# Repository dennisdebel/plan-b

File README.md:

Wemos Midi Roll Project
=====================================

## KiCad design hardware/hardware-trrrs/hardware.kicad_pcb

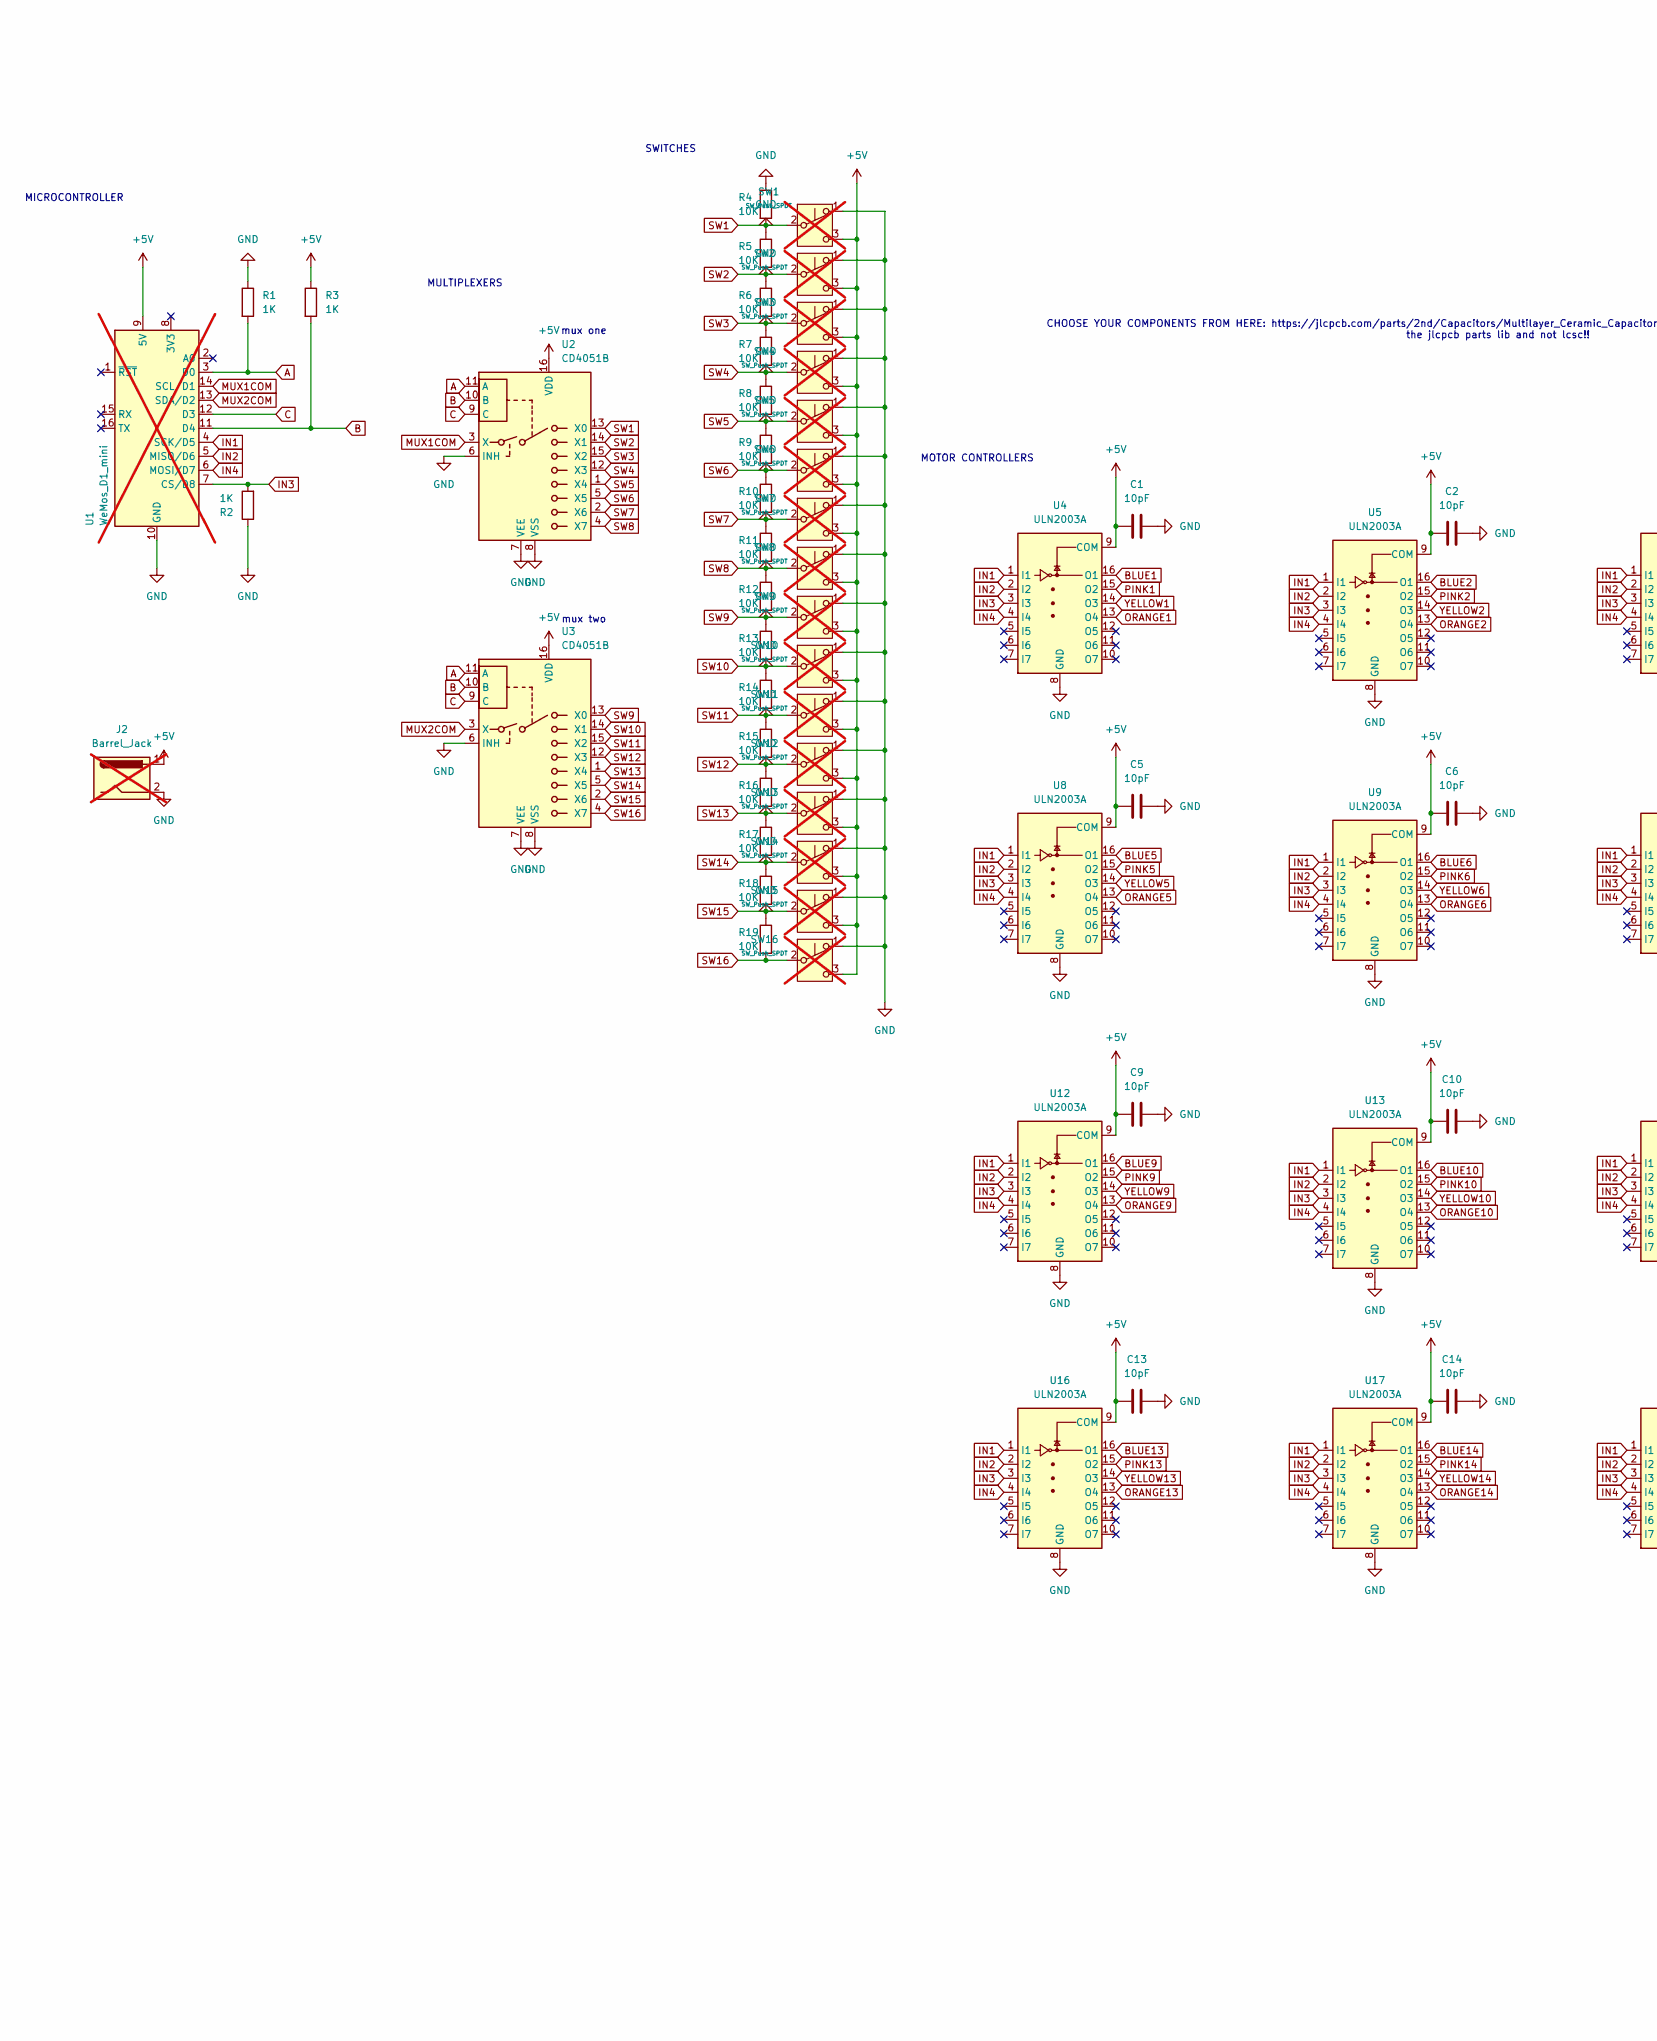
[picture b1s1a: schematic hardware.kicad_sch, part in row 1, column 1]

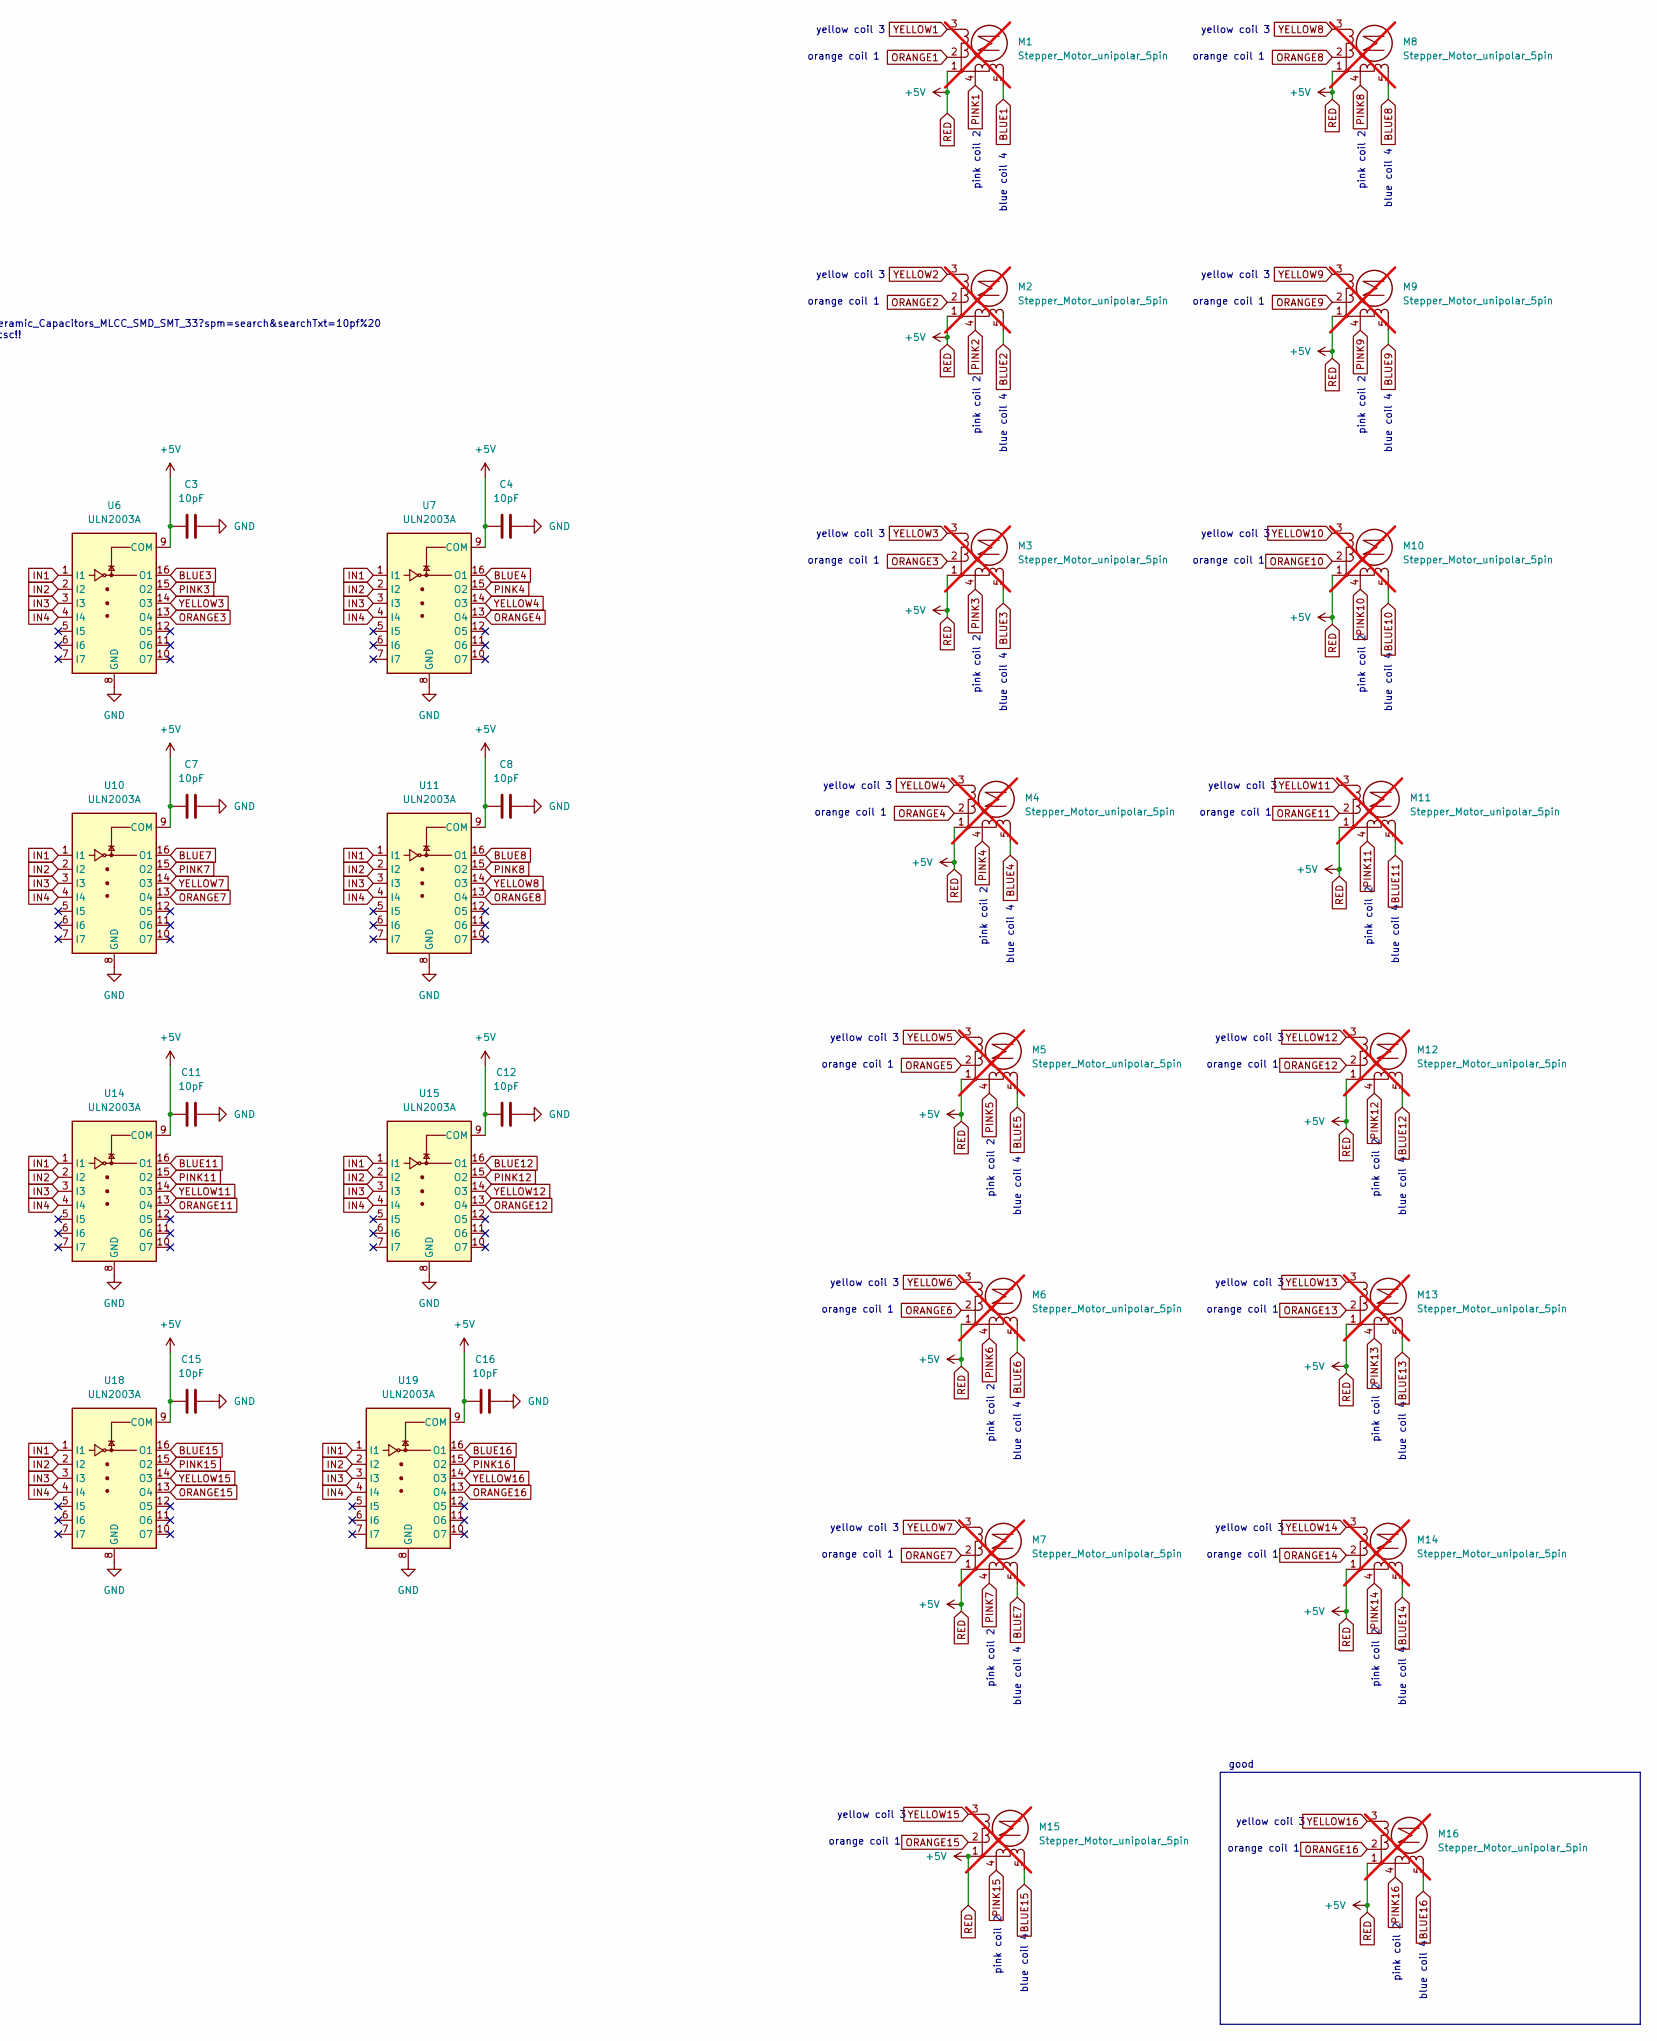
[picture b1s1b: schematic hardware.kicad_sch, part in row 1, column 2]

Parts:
C1, C2, C3, C4, C5, C6, C7, C8, C9, C10, C11, C12, C13, C14, C15, C16: 10pF; C_0402_1005Metric; LCSC PN C1545
J2: Barrel_Jack; BarrelJack_CUI_PJ-063AH_Horizontal; LCSC PN C22434582; not fitted
M1, M2, M3, M4, M5, M6, M7, M8, M9, M10, M11, M12, M13, M14, M15, M16: Stepper_Motor_unipolar_5pin; AUDIO-SMD_STX-3542-5N-G-TR; not fitted
R1, R2, R3: 1K; R_0805_2012Metric; LCSC PN C25623
R4, R5, R6, R7, R8, R9, R10, R11, R12, R13, R14, R15, R16, R17, R18, R19: 10K; R_0805_2012Metric; LCSC PN C2930231
SW1, SW2, SW3, SW4, SW5, SW6, SW7, SW8, SW9, SW10, SW11, SW12, SW13, SW14, SW15, SW16: SW_Push_SPDT; SW_MS0850502F030P1A-fixed; not fitted
U1: WeMos_D1_mini; WEMOS_D1_mini_light; not fitted
U2, U3: CD4051B; SOIC-16_3.9x9.9mm_P1.27mm; LCSC PN C21379
U4, U5, U6, U7, U8, U9, U10, U11, U12, U13, U14, U15, U16, U17, U18, U19: ULN2003A; SOIC-16_3.9x9.9mm_P1.27mm; LCSC PN C7512

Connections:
A: R1.2, U1.3 (D0), U2.11 (A), U3.11 (A)
B: R3.2, U1.11 (D4), U2.10 (B), U3.10 (B)
BLUE1: M1.5, U4.16 (O1)
BLUE2: M2.5, U5.16 (O1)
BLUE3: M3.5, U6.16 (O1)
BLUE4: M4.5, U7.16 (O1)
BLUE5: M5.5, U8.16 (O1)
BLUE6: M6.5, U9.16 (O1)
BLUE7: M7.5, U10.16 (O1)
BLUE8: M8.5, U11.16 (O1)
BLUE9: M9.5, U12.16 (O1)
BLUE10: M10.5, U13.16 (O1)
BLUE11: M11.5, U14.16 (O1)
BLUE12: M12.5, U15.16 (O1)
BLUE13: M13.5, U16.16 (O1)
BLUE14: M14.5, U17.16 (O1)
BLUE15: M15.5, U18.16 (O1)
BLUE16: M16.5, U19.16 (O1)
C: U1.12 (D3), U2.9 (C), U3.9 (C)
GND: C1.2, C2.2, C3.2, C4.2, C5.2, C6.2, C7.2, C8.2, C9.2, C10.2, C11.2, C12.2, C13.2, C14.2, C15.2, C16.2, J2.2, R1.1, R2.1, R4.1, R5.1, R6.1, R7.1, R8.1, R9.1, R10.1, R11.1, R12.1, R13.1, R14.1, R15.1, R16.1, R17.1, R18.1, R19.1, SW1.1 (A), SW2.1 (A), SW3.1 (A), SW4.1 (A), SW5.1 (A), SW6.1 (A), SW7.1 (A), SW8.1 (A), SW9.1 (A), SW10.1 (A), SW11.1 (A), SW12.1 (A), SW13.1 (A), SW14.1 (A), SW15.1 (A), SW16.1 (A), U1.10 (GND), U2.6 (INH), U2.7 (VEE), U2.8 (VSS), U3.6 (INH), U3.7 (VEE), U3.8 (VSS), U4.8 (GND), U5.8 (GND), U6.8 (GND), U7.8 (GND), U8.8 (GND), U9.8 (GND), U10.8 (GND), U11.8 (GND), U12.8 (GND), U13.8 (GND), U14.8 (GND), U15.8 (GND), U16.8 (GND), U17.8 (GND), U18.8 (GND), U19.8 (GND)
IN1: U1.4 (SCK/D5), U4.1 (I1), U5.1 (I1), U6.1 (I1), U7.1 (I1), U8.1 (I1), U9.1 (I1), U10.1 (I1), U11.1 (I1), U12.1 (I1), U13.1 (I1), U14.1 (I1), U15.1 (I1), U16.1 (I1), U17.1 (I1), U18.1 (I1), U19.1 (I1)
IN2: U1.5 (MISO/D6), U4.2 (I2), U5.2 (I2), U6.2 (I2), U7.2 (I2), U8.2 (I2), U9.2 (I2), U10.2 (I2), U11.2 (I2), U12.2 (I2), U13.2 (I2), U14.2 (I2), U15.2 (I2), U16.2 (I2), U17.2 (I2), U18.2 (I2), U19.2 (I2)
IN3: R2.2, U1.7 (CS/D8), U4.3 (I3), U5.3 (I3), U6.3 (I3), U7.3 (I3), U8.3 (I3), U9.3 (I3), U10.3 (I3), U11.3 (I3), U12.3 (I3), U13.3 (I3), U14.3 (I3), U15.3 (I3), U16.3 (I3), U17.3 (I3), U18.3 (I3), U19.3 (I3)
IN4: U1.6 (MOSI/D7), U4.4 (I4), U5.4 (I4), U6.4 (I4), U7.4 (I4), U8.4 (I4), U9.4 (I4), U10.4 (I4), U11.4 (I4), U12.4 (I4), U13.4 (I4), U14.4 (I4), U15.4 (I4), U16.4 (I4), U17.4 (I4), U18.4 (I4), U19.4 (I4)
MUX1COM: U1.14 (SCL/D1), U2.3 (X)
MUX2COM: U1.13 (SDA/D2), U3.3 (X)
ORANGE1: M1.2, U4.13 (O4)
ORANGE2: M2.2, U5.13 (O4)
ORANGE3: M3.2, U6.13 (O4)
ORANGE4: M4.2, U7.13 (O4)
ORANGE5: M5.2, U8.13 (O4)
ORANGE6: M6.2, U9.13 (O4)
ORANGE7: M7.2, U10.13 (O4)
ORANGE8: M8.2, U11.13 (O4)
ORANGE9: M9.2, U12.13 (O4)
ORANGE10: M10.2, U13.13 (O4)
ORANGE11: M11.2, U14.13 (O4)
ORANGE12: M12.2, U15.13 (O4)
ORANGE13: M13.2, U16.13 (O4)
ORANGE14: M14.2, U17.13 (O4)
ORANGE15: M15.2, U18.13 (O4)
ORANGE16: M16.2, U19.13 (O4)
PINK1: M1.4, U4.15 (O2)
PINK2: M2.4, U5.15 (O2)
PINK3: M3.4, U6.15 (O2)
PINK4: M4.4, U7.15 (O2)
PINK5: M5.4, U8.15 (O2)
PINK6: M6.4, U9.15 (O2)
PINK7: M7.4, U10.15 (O2)
PINK8: M8.4, U11.15 (O2)
PINK9: M9.4, U12.15 (O2)
PINK10: M10.4, U13.15 (O2)
PINK11: M11.4, U14.15 (O2)
PINK12: M12.4, U15.15 (O2)
PINK13: M13.4, U16.15 (O2)
PINK14: M14.4, U17.15 (O2)
PINK15: M15.4, U18.15 (O2)
PINK16: M16.4, U19.15 (O2)
RED: C1.1, C2.1, C3.1, C4.1, C5.1, C6.1, C7.1, C8.1, C9.1, C10.1, C11.1, C12.1, C13.1, C14.1, C15.1, C16.1, J2.1, M1.1, M2.1, M3.1, M4.1, M5.1, M6.1, M7.1, M8.1, M9.1, M10.1, M11.1, M12.1, M13.1, M14.1, M15.1, M16.1, R3.1, SW1.3 (C), SW2.3 (C), SW3.3 (C), SW4.3 (C), SW5.3 (C), SW6.3 (C), SW7.3 (C), SW8.3 (C), SW9.3 (C), SW10.3 (C), SW11.3 (C), SW12.3 (C), SW13.3 (C), SW14.3 (C), SW15.3 (C), SW16.3 (C), U1.9 (5V), U2.16 (VDD), U3.16 (VDD), U4.9 (COM), U5.9 (COM), U6.9 (COM), U7.9 (COM), U8.9 (COM), U9.9 (COM), U10.9 (COM), U11.9 (COM), U12.9 (COM), U13.9 (COM), U14.9 (COM), U15.9 (COM), U16.9 (COM), U17.9 (COM), U18.9 (COM), U19.9 (COM)
SW1: R4.2, SW1.2 (B), U2.13 (X0)
SW2: R5.2, SW2.2 (B), U2.14 (X1)
SW3: R6.2, SW3.2 (B), U2.15 (X2)
SW4: R7.2, SW4.2 (B), U2.12 (X3)
SW5: R8.2, SW5.2 (B), U2.1 (X4)
SW6: R9.2, SW6.2 (B), U2.5 (X5)
SW7: R10.2, SW7.2 (B), U2.2 (X6)
SW8: R11.2, SW8.2 (B), U2.4 (X7)
SW9: R12.2, SW9.2 (B), U3.13 (X0)
SW10: R13.2, SW10.2 (B), U3.14 (X1)
SW11: R14.2, SW11.2 (B), U3.15 (X2)
SW12: R15.2, SW12.2 (B), U3.12 (X3)
SW13: R16.2, SW13.2 (B), U3.1 (X4)
SW14: R17.2, SW14.2 (B), U3.5 (X5)
SW15: R18.2, SW15.2 (B), U3.2 (X6)
SW16: R19.2, SW16.2 (B), U3.4 (X7)
YELLOW1: M1.3 (-), U4.14 (O3)
YELLOW2: M2.3 (-), U5.14 (O3)
YELLOW3: M3.3 (-), U6.14 (O3)
YELLOW4: M4.3 (-), U7.14 (O3)
YELLOW5: M5.3 (-), U8.14 (O3)
YELLOW6: M6.3 (-), U9.14 (O3)
YELLOW7: M7.3 (-), U10.14 (O3)
YELLOW8: M8.3 (-), U11.14 (O3)
YELLOW9: M9.3 (-), U12.14 (O3)
YELLOW10: M10.3 (-), U13.14 (O3)
YELLOW11: M11.3 (-), U14.14 (O3)
YELLOW12: M12.3 (-), U15.14 (O3)
YELLOW13: M13.3 (-), U16.14 (O3)
YELLOW14: M14.3 (-), U17.14 (O3)
YELLOW15: M15.3 (-), U18.14 (O3)
YELLOW16: M16.3 (-), U19.14 (O3)

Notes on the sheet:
pink coil 2
blue coil 4
yellow coil 3
orange coil 1
MICROCONTROLLER
mux two
good
SWITCHES
MOTOR CONTROLLERS
CHOOSE YOUR COMPONENTS FROM HERE: https://jlcpcb.com/parts/2nd/Capacitors/Multilayer_Ceramic_Capacitors_MLCC_SMD_SMT_33?spm=search&searchTxt=10pf%20 the jlcpcb parts lib and not lcsc!!
MULTIPLEXERS
mux one

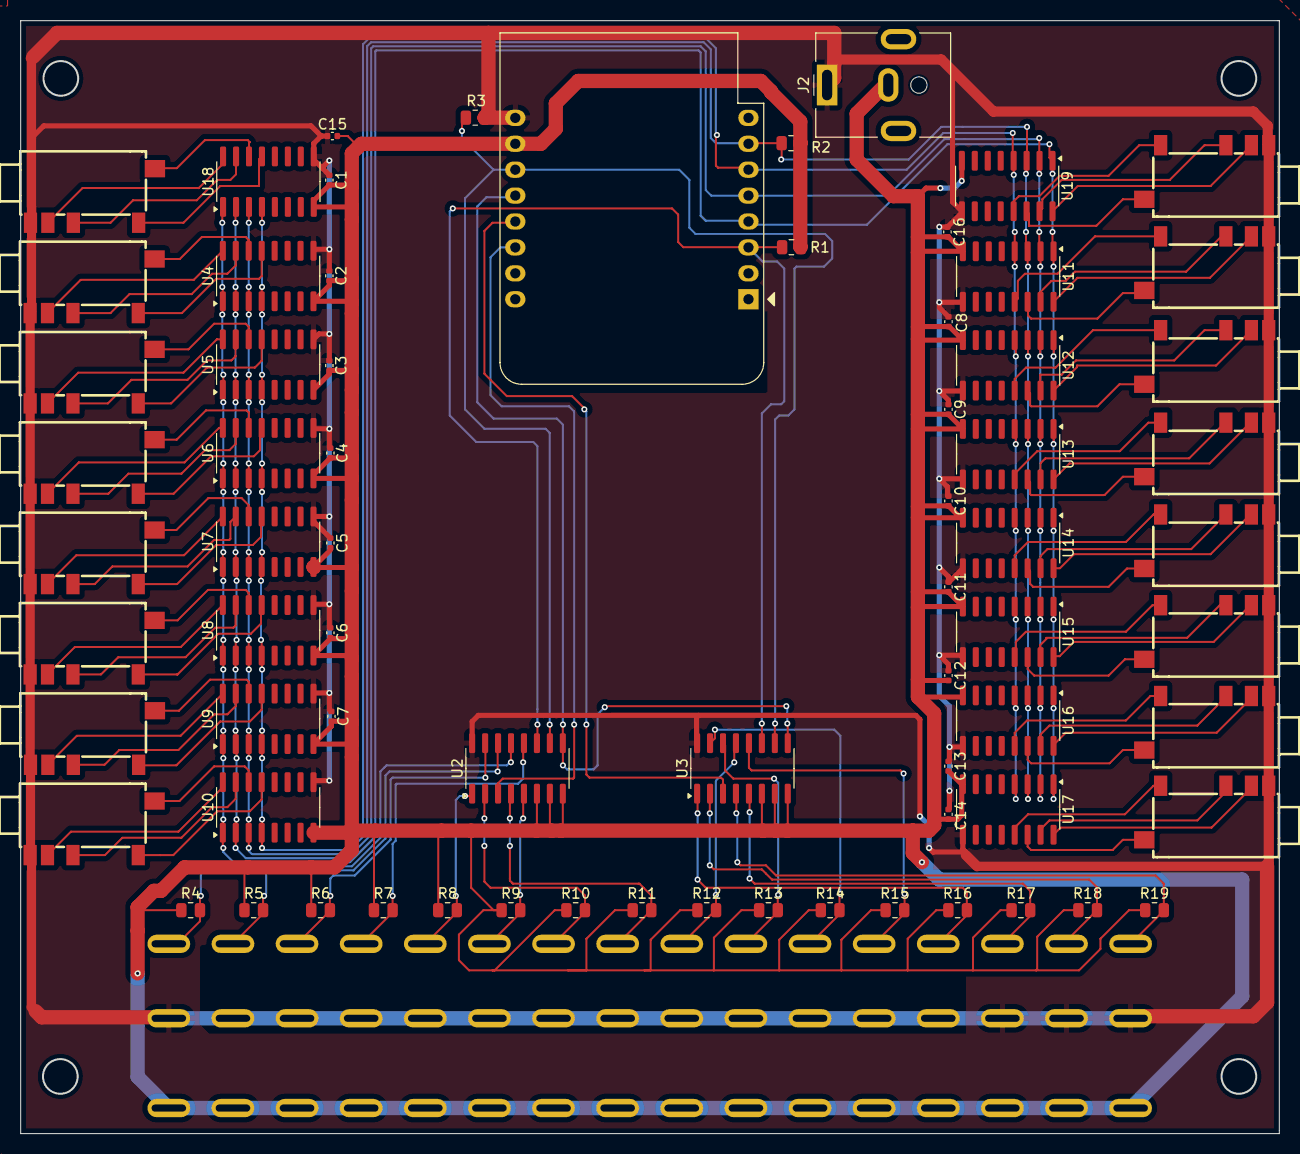
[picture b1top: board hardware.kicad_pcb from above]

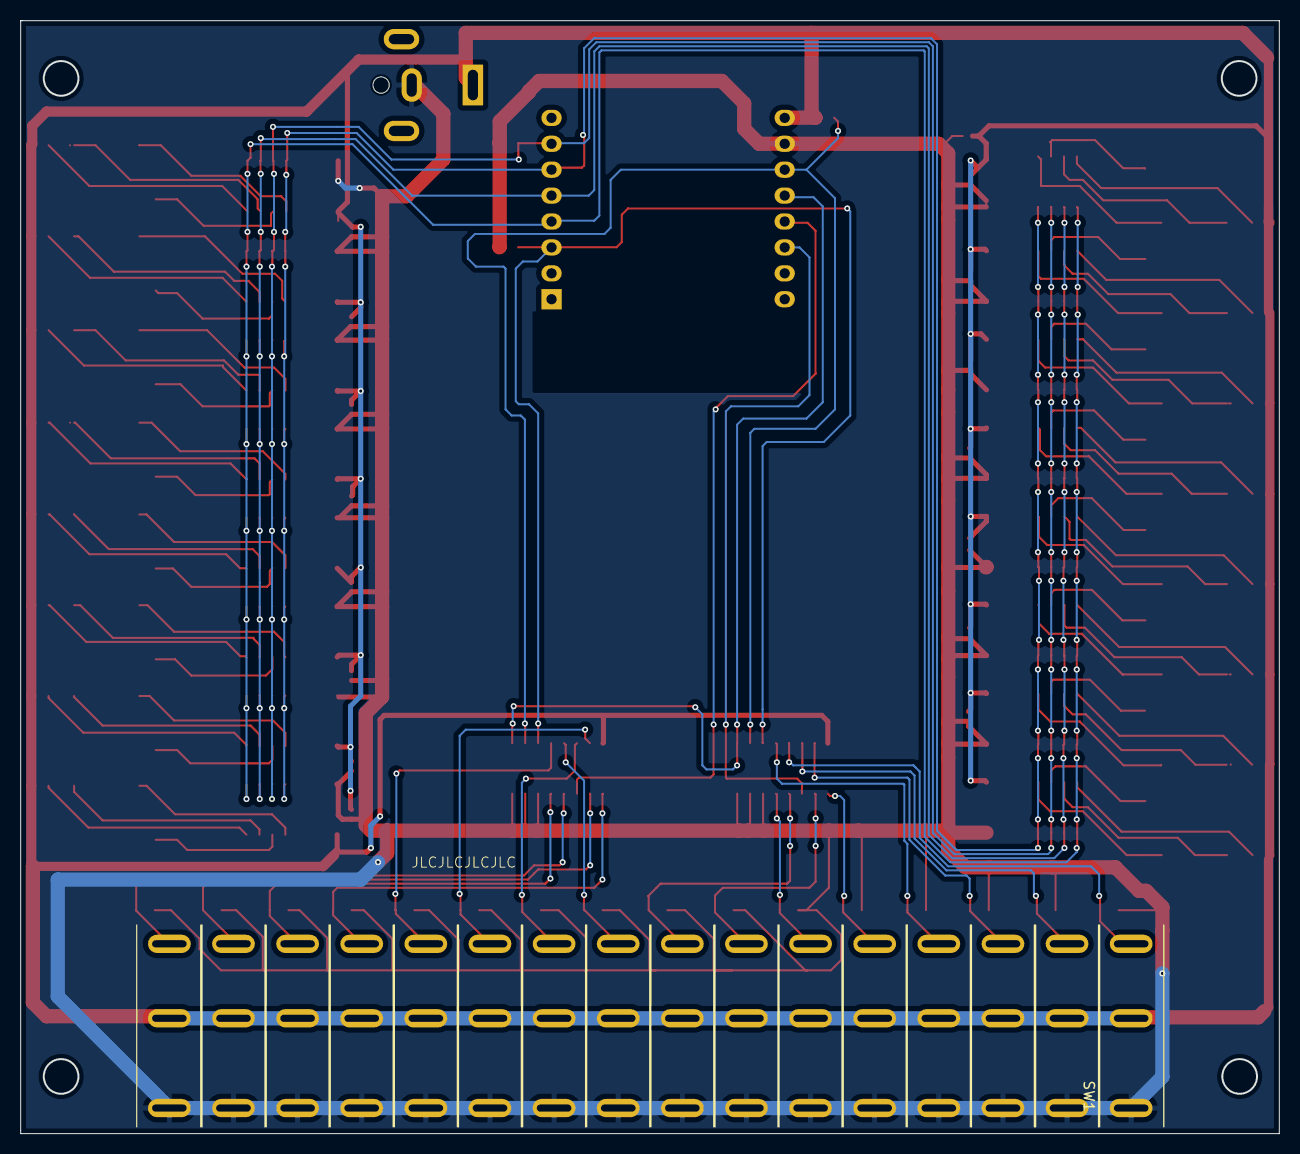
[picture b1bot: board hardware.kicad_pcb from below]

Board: 2 copper layers, 123.3 x 109.0 mm, 87 parts (16 on the bottom side), 91 nets.

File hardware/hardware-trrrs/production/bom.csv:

Comment,Designator,Footprint,LCSC
10pF,"C1, C10, C11, C12, C13, C14, C2, C3, C4, C5, C6, C7, C8, C9",805,C157608
Barrel_Jack,J2,BarrelJack_CUI_PJ-063AH_Horizontal,C22434582
Stepper_Motor_unipolar_5pin,"M1, M10, M11, M12, M13, M14, M2, M3, M4, M5, M6, M7, M8, M9",HOOYA-PJ-3505A_C19190915-Jack_3.5mm_PJ31060-I_Horizontal,C19190915
1K,"R1, R2, R3",805,C25623
10K,"R10, R11, R12, R13, R14, R15, R16, R17, R18, R19, R4, R5, R6, R7, R8, R9",805,C2930231
ULN2003A,"U10, U11, U12, U13, U14, U15, U16, U17, U4, U5, U6, U7, U8, U9",SOIC-16_3.9x9.9mm_P1.27mm,C7512
CD4051B,"U2, U3",SOIC-16_3.9x9.9mm_P1.27mm,C21379

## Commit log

2024-05-31 Added test for looping over the muxes
2024-06-03 fixed off by one error
2024-06-03 added more human readable pin values
2024-06-04 Added second mux
2024-06-04 added button readings and osc lib
2024-06-04 added debug flag
2024-06-05 added osc udp noteon message after button press, removed osc dep
2024-07-02 Added support for all the buttons/notes
2024-07-03 Added noteOff
2024-07-03 added debug info for noteOff message
2024-07-07 Removed note repeats, added noteOff on release, added disable/enable wifi flag
2024-07-08 added midi channel selection
2024-07-16 Added note and channel user configs
2024-07-19 fixed channel error and button offset in muxTwo
2024-07-22 Fixed NoteOn/Off channel issue
    Fixed issue where NoteOn was using the wrong counter to look up the correct NoteOn channel number. Also cleaned up the code and some debugging beautification
2024-07-23 Fixed off by one error in muxTwo
2024-10-17 added documentation, start stepper code and schematic
2024-10-19 added stepper test code
    moved muxes to other pins, deleted debugging (caused issues)
2024-10-19 updated schematic
2024-10-19 added 2 more motors and controllers
2024-11-07 added continuous stepper code
2024-11-14 Added latest schematic and pcb design
2024-11-18 added continuous rotation to stepper
2024-12-16 added final pcb design
2024-12-16 updated pcb design
2024-12-17 made a jst version of the pcb
2024-12-17 partial jst conversion of pcb
2024-12-17 half way done
2024-12-18 finalised JST switch version of the pcb
2024-12-18 reorganisation
2025-01-01 Code: Added debug led (wifi)
2025-02-21 rotated switches on jst edition
2025-02-21 added new pcb revision (trrrs)
2025-02-22 Added do not populate flag to trrrs jacks
2025-03-09 Added production files (Pick and Place) for JLCPCB
2025-03-13 Updated pcb
2025-06-10 Added start/stop, refactor muxread
    Still much to do
2025-06-18 many updates (timer, off button cheat)
2025-06-30 fixed start stop issues and stop button ignore time window
2025-07-20 fixed UDP buffer issues
